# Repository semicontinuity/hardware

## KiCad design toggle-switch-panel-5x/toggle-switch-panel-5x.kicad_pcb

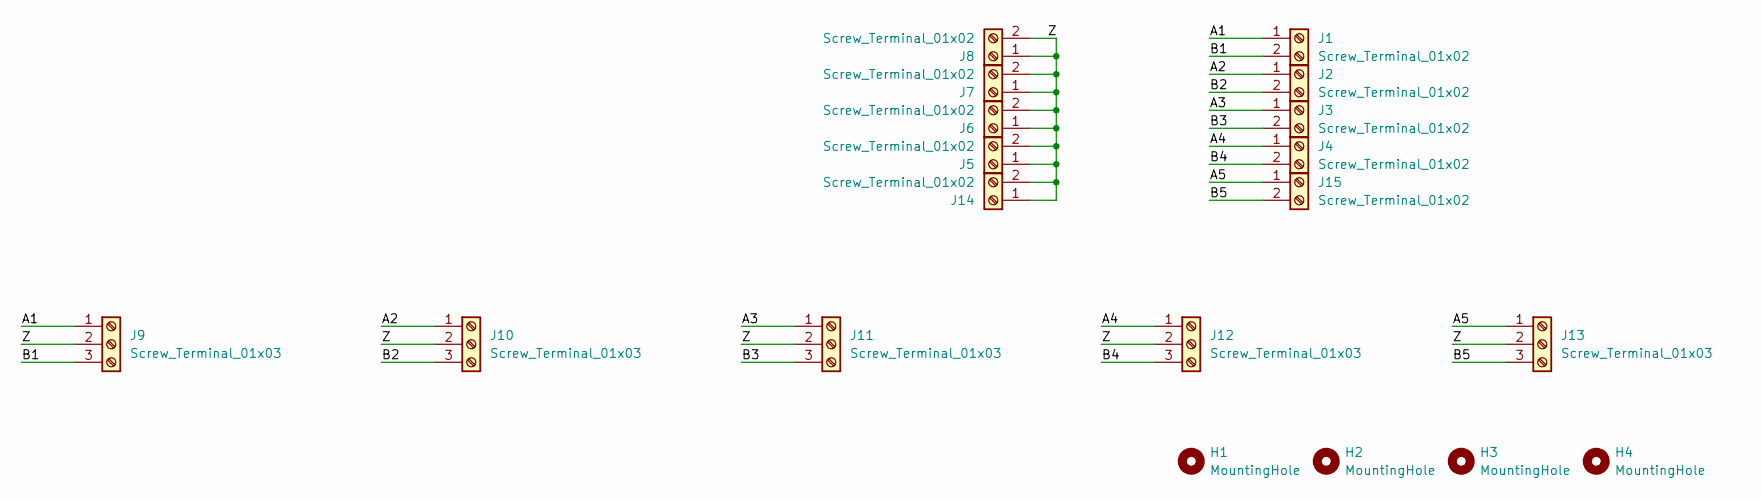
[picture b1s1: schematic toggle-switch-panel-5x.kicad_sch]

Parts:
H1, H2, H3, H4: MountingHole; MountingHole_3.2mm_M3
J1, J2, J3, J4, J5, J6, J7, J8, J14, J15: Screw_Terminal_01x02; TerminalBlock_Phoenix_MKDS-1,5-2_1x02_P5.00mm_Horizontal
J9, J10, J11, J12, J13: Screw_Terminal_01x03; TerminalBlock_Phoenix_MKDS-1,5-3_1x03_P5.00mm_Horizontal

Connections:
/A1: J1.1, J9.1
/A2: J2.1, J10.1
/A3: J3.1, J11.1
/A4: J4.1, J12.1
/A5: J13.1, J15.1
/B1: J1.2, J9.3
/B2: J2.2, J10.3
/B3: J3.2, J11.3
/B4: J4.2, J12.3
/B5: J13.3, J15.2
/Z: J5.1, J5.2, J6.1, J6.2, J7.1, J7.2, J8.1, J8.2, J9.2, J10.2, J11.2, J12.2, J13.2, J14.1, J14.2

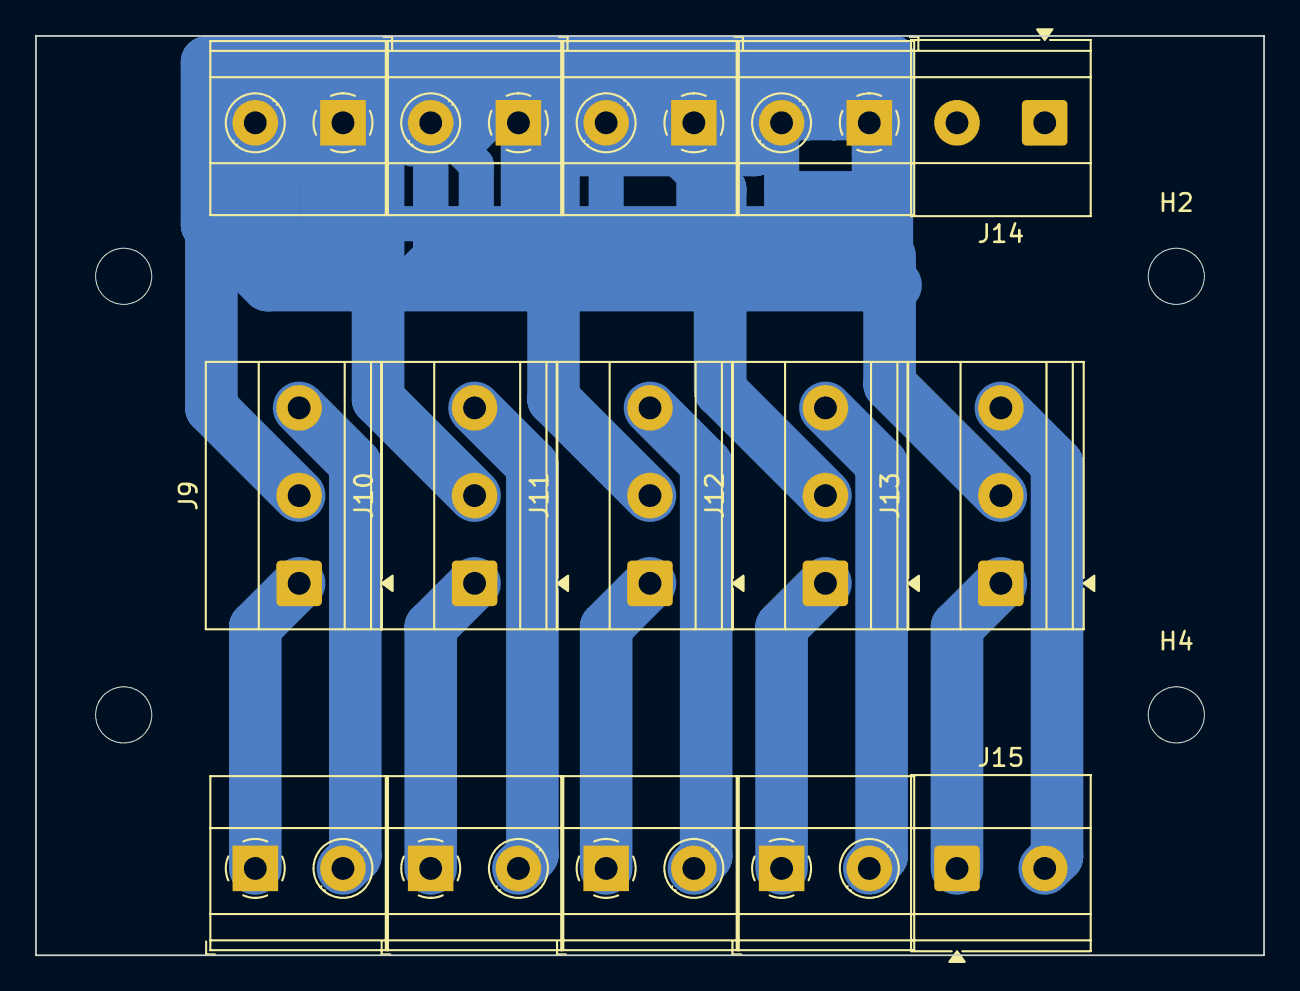
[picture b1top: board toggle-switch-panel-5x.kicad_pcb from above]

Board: 2 copper layers, 70.0 x 52.4 mm, 19 parts (0 on the bottom side), 11 nets.

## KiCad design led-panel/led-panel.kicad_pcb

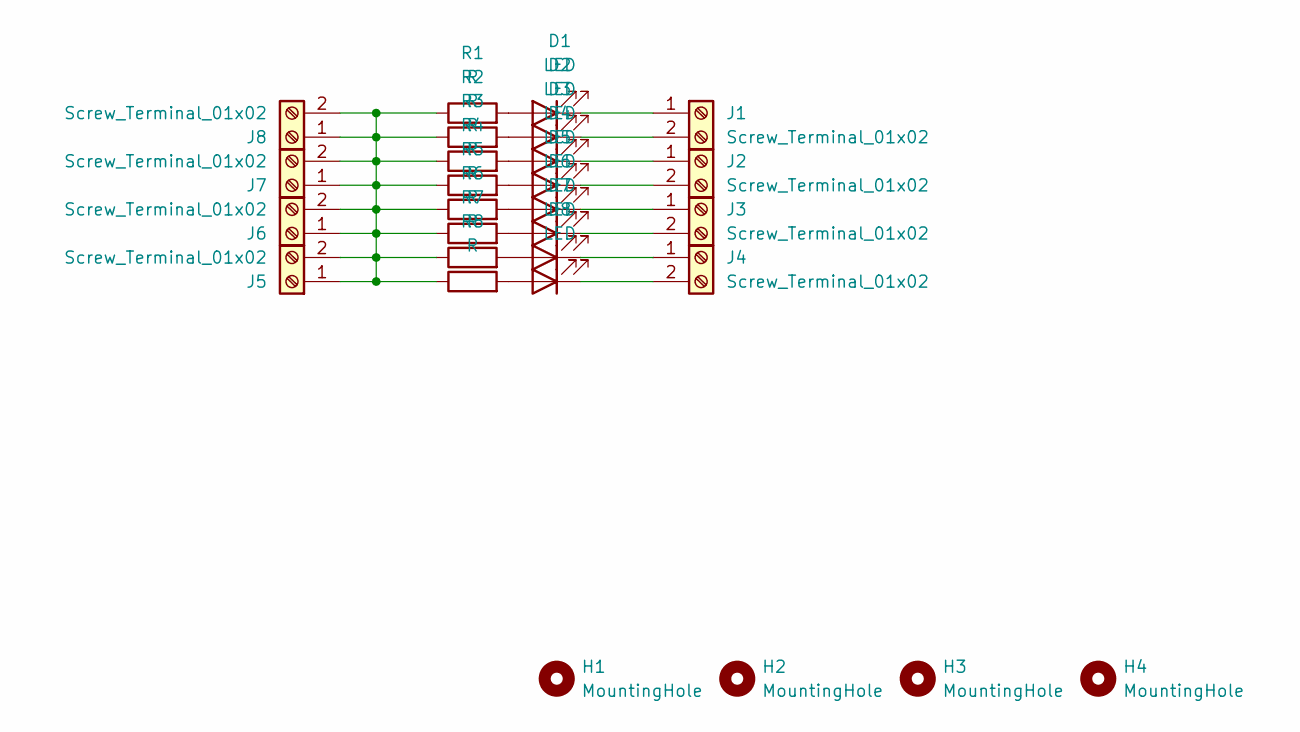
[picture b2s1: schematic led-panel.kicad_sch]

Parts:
D1, D2, D3, D4, D5, D6, D7, D8: LED; LED_D3.0mm
H1, H2, H3, H4: MountingHole; MountingHole_3.2mm_M3
J1, J2, J3, J4, J5, J6, J7, J8: Screw_Terminal_01x02; TerminalBlock_Phoenix_MKDS-1,5-2_1x02_P5.00mm_Horizontal
R1, R2, R3, R4, R5, R6, R7, R8: R; R_Axial_DIN0411_L9.9mm_D3.6mm_P20.32mm_Horizontal

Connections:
unnamed: D1.2 (A), R1.2
unnamed: D1.1 (K), J1.1
unnamed: D2.2 (A), R2.2
unnamed: D2.1 (K), J1.2
unnamed: D3.2 (A), R3.2
unnamed: D3.1 (K), J2.1
unnamed: D4.2 (A), R4.2
unnamed: D4.1 (K), J2.2
unnamed: D5.2 (A), R5.2
unnamed: D5.1 (K), J3.1
unnamed: D6.2 (A), R6.2
unnamed: D6.1 (K), J3.2
unnamed: D7.2 (A), R7.2
unnamed: D7.1 (K), J4.1
unnamed: D8.2 (A), R8.2
unnamed: D8.1 (K), J4.2
unnamed: J5.1, J5.2, J6.1, J6.2, J7.1, J7.2, J8.1, J8.2, R1.1, R2.1, R3.1, R4.1, R5.1, R6.1, R7.1, R8.1

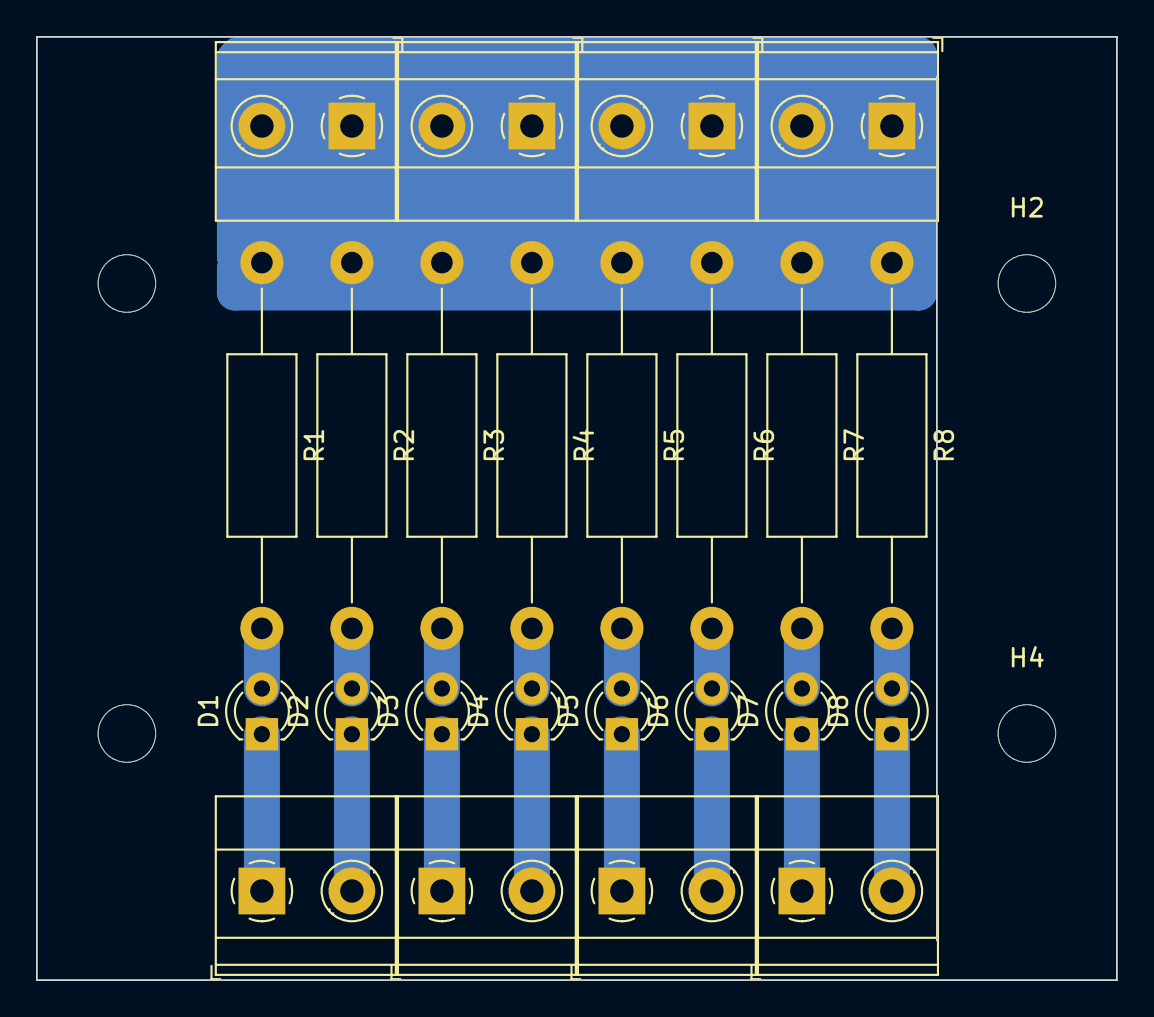
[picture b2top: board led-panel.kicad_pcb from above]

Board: 2 copper layers, 60.0 x 52.4 mm, 28 parts (0 on the bottom side), 17 nets.

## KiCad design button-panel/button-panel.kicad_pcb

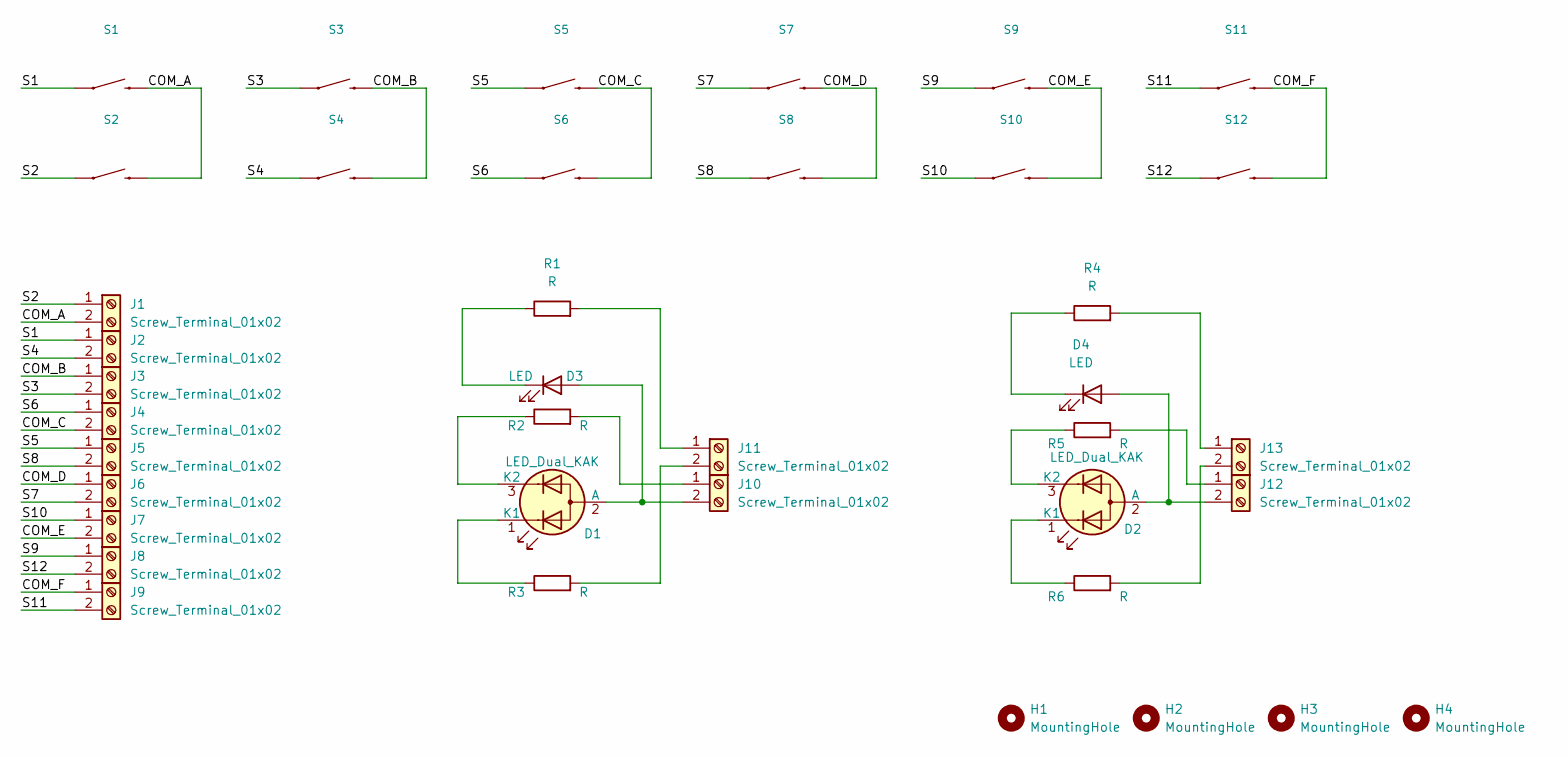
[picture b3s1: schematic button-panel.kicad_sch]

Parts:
D1, D2: LED_Dual_KAK; LED_D3.0mm-3
D3, D4: LED; LED_D3.0mm
H1, H2, H3, H4: MountingHole; MountingHole_3.2mm_M3
J1, J2, J3, J4, J5, J6, J7, J8, J9: Screw_Terminal_01x02; TerminalBlock_Phoenix_MKDS-1,5-2_1x02_P5.00mm_Horizontal
J10, J11, J12, J13: Screw_Terminal_01x02; TerminalBlock_Phoenix_PT-1,5-2-3.5-H_1x02_P3.50mm_Horizontal
R1, R2, R3, R4, R5, R6: R; R_0805_2012Metric
S1, S2, S3, S4, S5, S6, S7, S8, S9, S10, S11, S12: MOMENTARY-SWITCH-SPST-PTH-12MM; SW_PUSH-12mm

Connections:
/COM_A: J1.2, S1.2, S2.2
/COM_B: J3.1, S3.2, S4.2
/COM_C: J4.2, S5.2, S6.2
/COM_D: J6.1, S7.2, S8.2
/COM_E: J7.2, S9.2, S10.2
/COM_F: J9.1, S11.2, S12.2
/S1: J2.1, S1.1
/S2: J1.1, S2.1
/S3: J3.2, S3.1
/S4: J2.2, S4.1
/S5: J5.1, S5.1
/S6: J4.1, S6.1
/S7: J6.2, S7.1
/S8: J5.2, S8.1
/S9: J8.1, S9.1
/S10: J7.1, S10.1
/S11: J9.2, S11.1
/S12: J8.2, S12.1
unnamed: D1.1 (K1), R3.1
unnamed: D1.2 (A), D3.2 (A), J10.2
unnamed: D1.3 (K2), R2.1
unnamed: D2.1 (K1), R6.1
unnamed: D2.3 (K2), R5.1
unnamed: D3.1 (K), R1.1
unnamed: D4.1 (K), R4.1
unnamed: J10.1, R2.2
unnamed: J11.1, R1.2
unnamed: J11.2, R3.2
unnamed: J12.1, R5.2
unnamed: D2.2 (A), D4.2 (A), J12.2
unnamed: J13.1, R4.2
unnamed: J13.2, R6.2

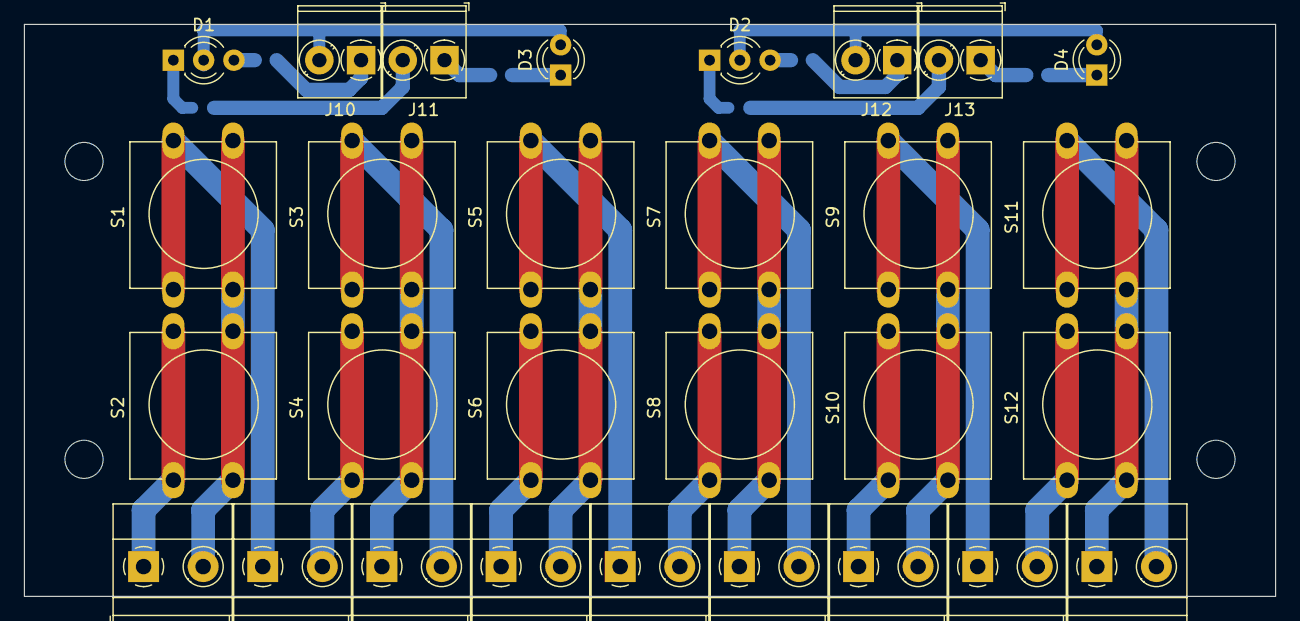
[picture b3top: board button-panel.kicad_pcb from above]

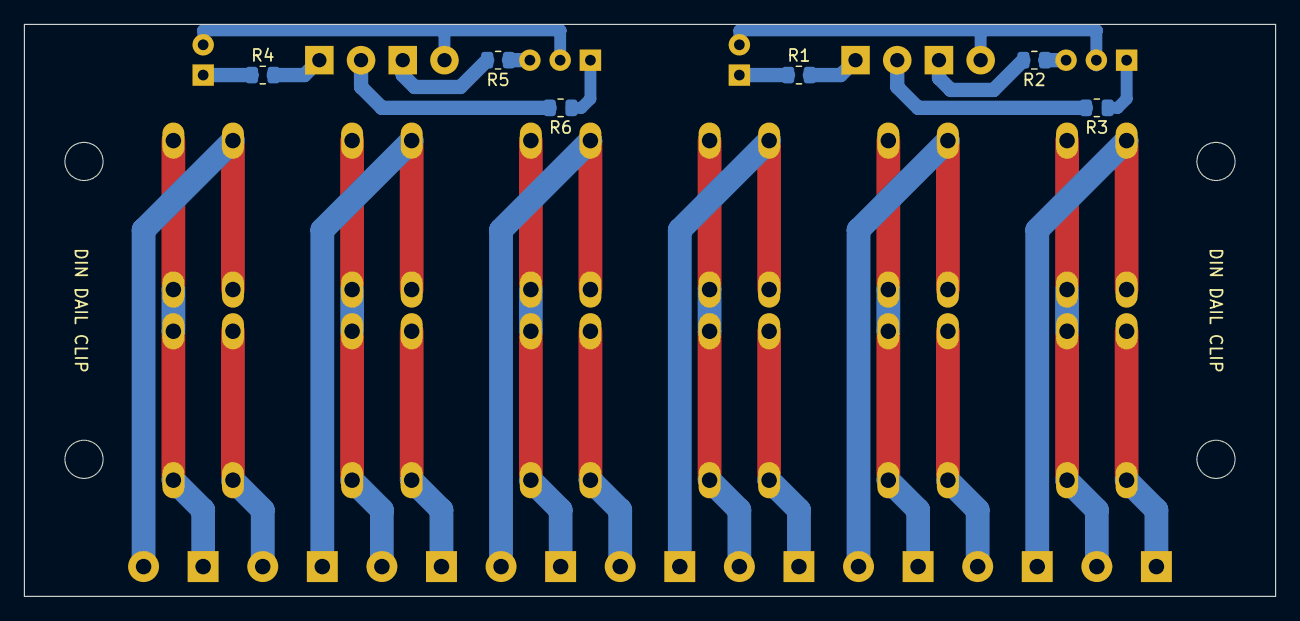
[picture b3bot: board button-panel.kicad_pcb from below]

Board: 2 copper layers, 105.0 x 48.0 mm, 39 parts (6 on the bottom side), 32 nets.

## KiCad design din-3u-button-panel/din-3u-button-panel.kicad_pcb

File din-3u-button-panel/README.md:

#### UI and connections

* 3U DIN rail enclosure (51mm)

Base board
```
   LED_A  LED_B  LED_C  VCC  VCC  LED_D  LED_E  LED_F
+--------------------------------------------------------+
|                                                        |
|                                                        |
|                                                        |
|                                                        |
|                                                        |
|                                                        |
|                                                        |
+--------------------------------------------------------+
   BTN_A  BTN_B  BTN_C  GND  GND  BTN_D  BTN_E  BTN_F

```

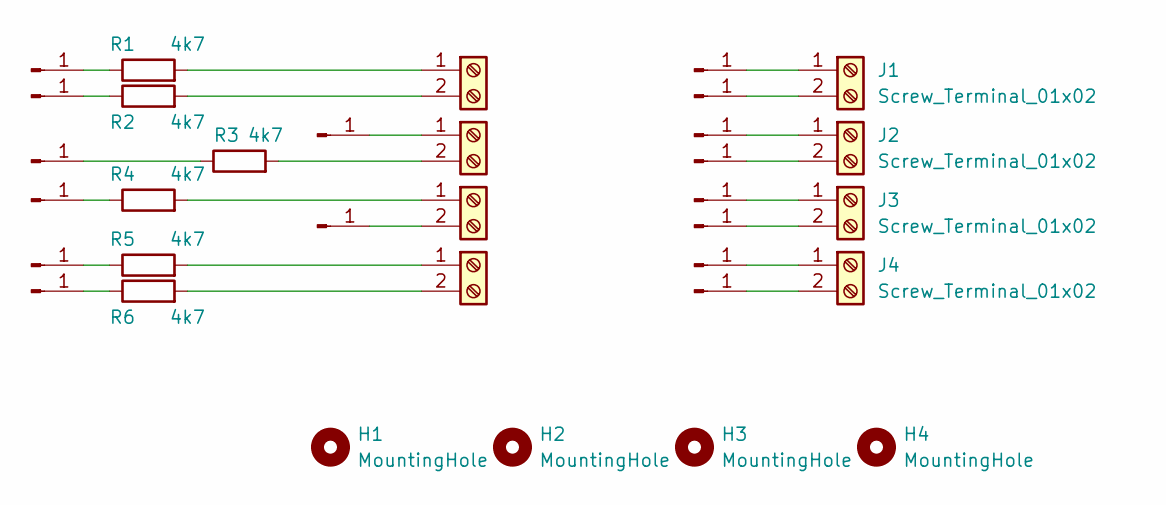
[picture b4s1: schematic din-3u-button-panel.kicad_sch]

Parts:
H1, H2, H3, H4: MountingHole; MountingHole_3.5mm
J1, J2, J3, J4: Screw_Terminal_01x02; TerminalBlock_Phoenix_MKDS-1,5-2-5.08_1x02_P5.08mm_Horizont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
J5, J10, J11, J12, J13, J14, J15, J16, J17, J18, J19, J20, J21, J22, J23, J24: Conn_01x01_Pin; Pin_D1.0mm_L10.0mm
J6: Z1; TerminalBlock_Phoenix_MKDS-1,5-2-5.08_1x02_P5.08mm_Horizont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
J7: Z2; TerminalBlock_Phoenix_MKDS-1,5-2-5.08_1x02_P5.08mm_Horizont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
J8: Z3; TerminalBlock_Phoenix_MKDS-1,5-2-5.08_1x02_P5.08mm_Horizont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
J9: Z4; TerminalBlock_Phoenix_MKDS-1,5-2-5.08_1x02_P5.08mm_Horizont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
R1, R2, R3, R4, R5, R6: 4k7; R_Axial_DIN0207_L6.3mm_D2.5mm_P15.24mm_Horizontal

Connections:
unnamed: J1.1, J17.1
unnamed: J1.2, J18.1
unnamed: J2.2, J20.1
unnamed: J5.1, R1.1
unnamed: J6.1, R1.2
unnamed: J6.2, R2.2
unnamed: J7.2, R3.2
unnamed: J8.1, R4.2
unnamed: J9.1, R5.2
unnamed: J9.2, R6.2
unnamed: J10.1, R2.1
unnamed: J7.1, J11.1
unnamed: J12.1, R3.1
unnamed: J13.1, R4.1
unnamed: J8.2, J14.1
unnamed: J15.1, R5.1
unnamed: J16.1, R6.1
unnamed: J2.1, J19.1
unnamed: J3.1, J21.1
unnamed: J3.2, J22.1
unnamed: J4.1, J23.1
unnamed: J4.2, J24.1

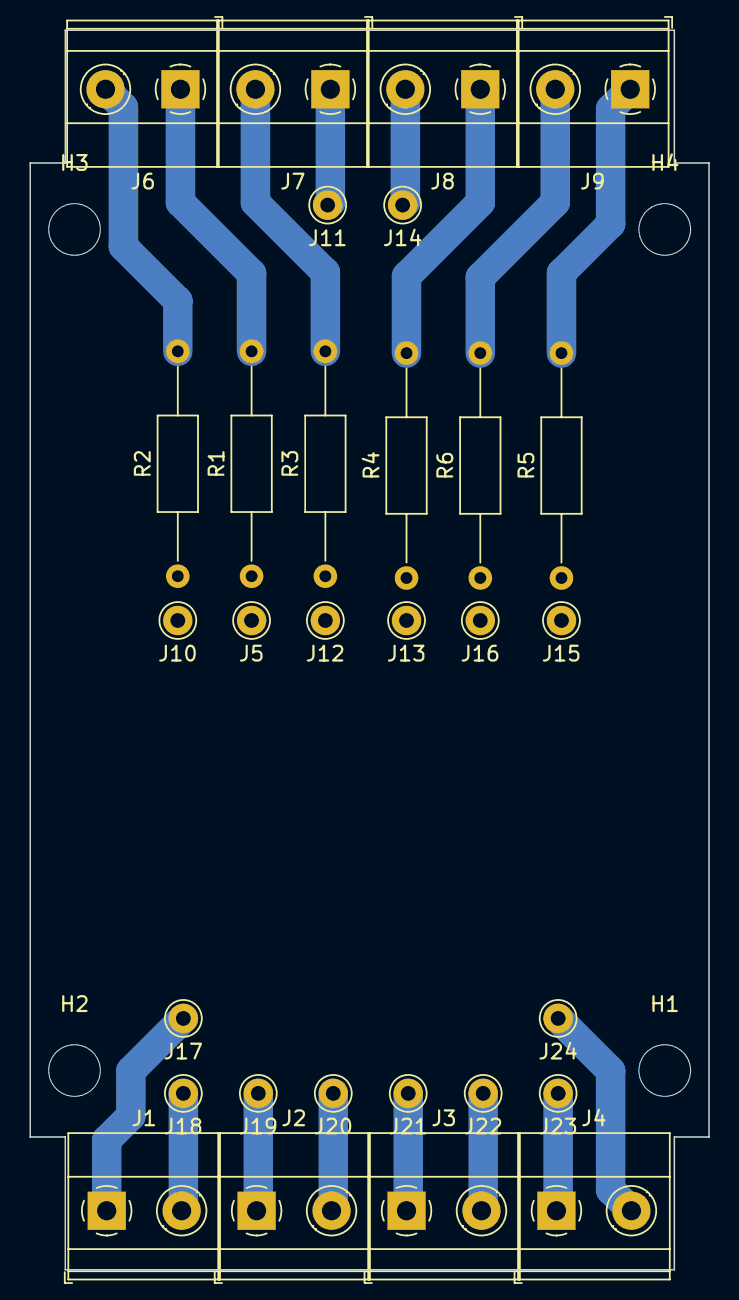
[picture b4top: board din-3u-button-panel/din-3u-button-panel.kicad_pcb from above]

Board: 2 copper layers, 46.0 x 84.0 mm, 34 parts (0 on the bottom side), 22 nets.

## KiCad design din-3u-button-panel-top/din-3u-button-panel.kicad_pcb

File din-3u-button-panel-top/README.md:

#### UI and connections

* 3U DIN rail enclosure (51mm)

Front panel
```
+--------------------------------------------------------+
|                                                        |
|  (A) Yellow          (B) Yellow         (C) Red        | --
|                                                        | 16mm
|  (D) Green           (E) Green          (F) White      | --
|                                                        |
+--------------------------------------------------------+
    |       16mm       |
```

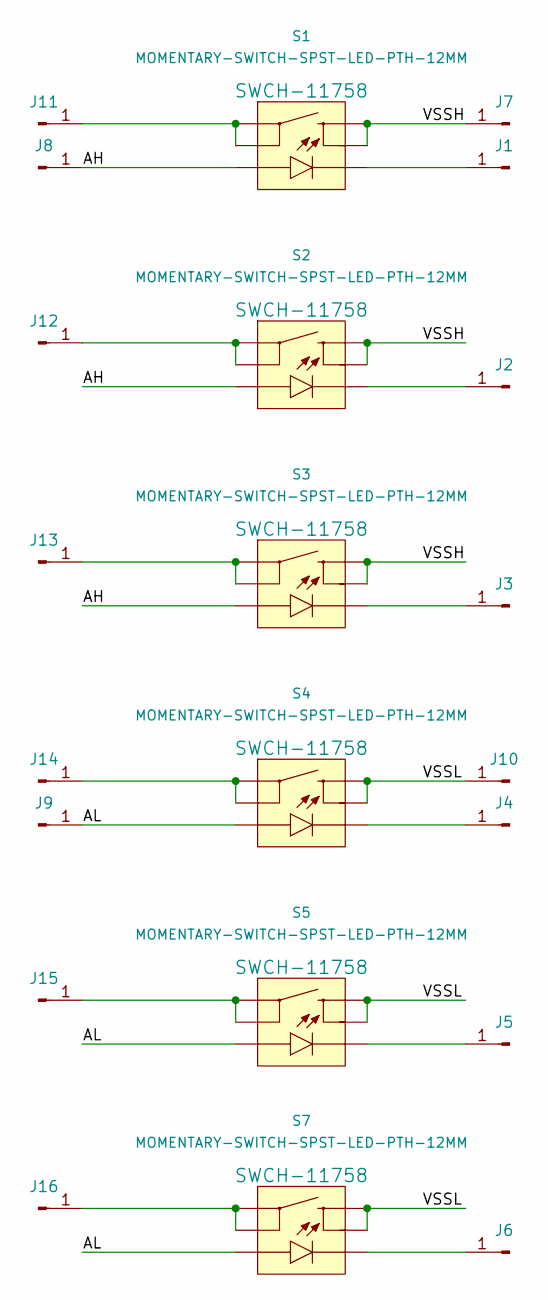
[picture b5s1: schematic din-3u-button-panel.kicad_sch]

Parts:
J1, J2, J3, J4, J5, J6, J7, J8, J9, J10, J11, J12, J13, J14, J15, J16: Conn_01x01_Pin; PinHeader_1x01_P2.54mm_Vertical
S1, S2, S3, S4, S5, S7: MOMENTARY-SWITCH-SPST-LED-PTH-12MM; TACTILE_SWITCH_LED_PTH_12MM

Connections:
/AH: J8.1, S1.A, S2.A, S3.A
/AL: J9.1, S4.A, S5.A, S7.A
/VSSH: J7.1, S1.1, S1.2, S2.1, S2.2, S3.1, S3.2
/VSSL: J10.1, S4.1, S4.2, S5.1, S5.2, S7.1, S7.2
unnamed: J1.1, S1.C
unnamed: J2.1, S2.C
unnamed: J3.1, S3.C
unnamed: J4.1, S4.C
unnamed: J5.1, S5.C
unnamed: J6.1, S7.C
unnamed: J11.1, S1.3, S1.4 (1)
unnamed: J12.1, S2.3, S2.4 (1)
unnamed: J13.1, S3.3, S3.4 (1)
unnamed: J14.1, S4.3, S4.4 (1)
unnamed: J15.1, S5.3, S5.4 (1)
unnamed: J16.1, S7.3, S7.4 (1)

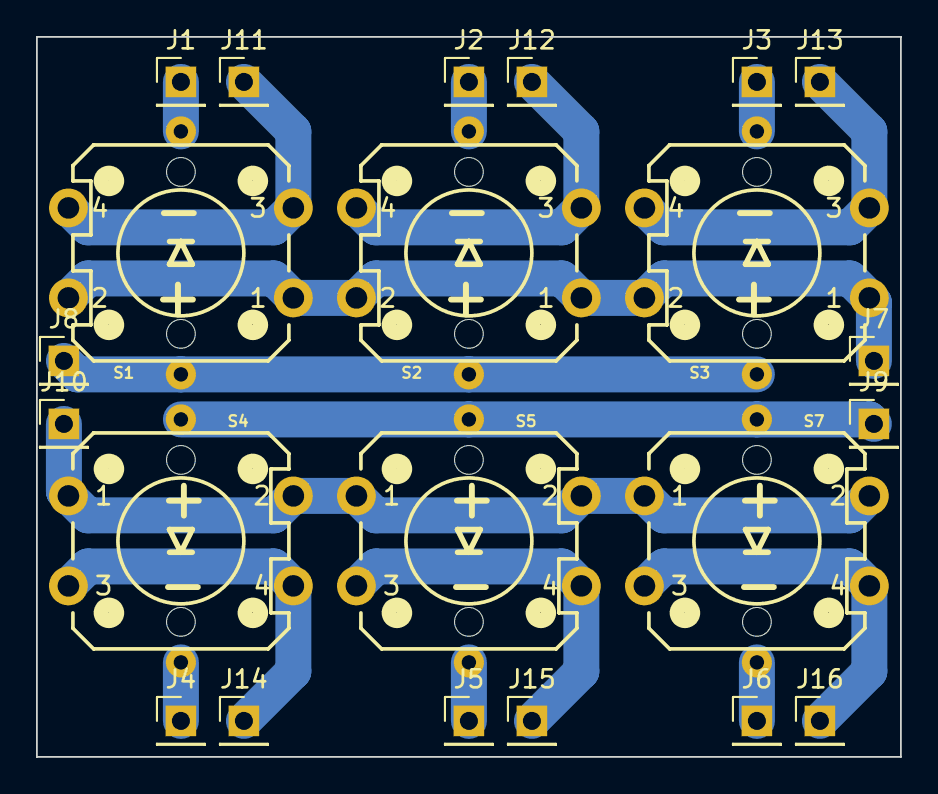
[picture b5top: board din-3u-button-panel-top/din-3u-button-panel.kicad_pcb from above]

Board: 2 copper layers, 48.0 x 40.0 mm, 22 parts (0 on the bottom side), 16 nets.

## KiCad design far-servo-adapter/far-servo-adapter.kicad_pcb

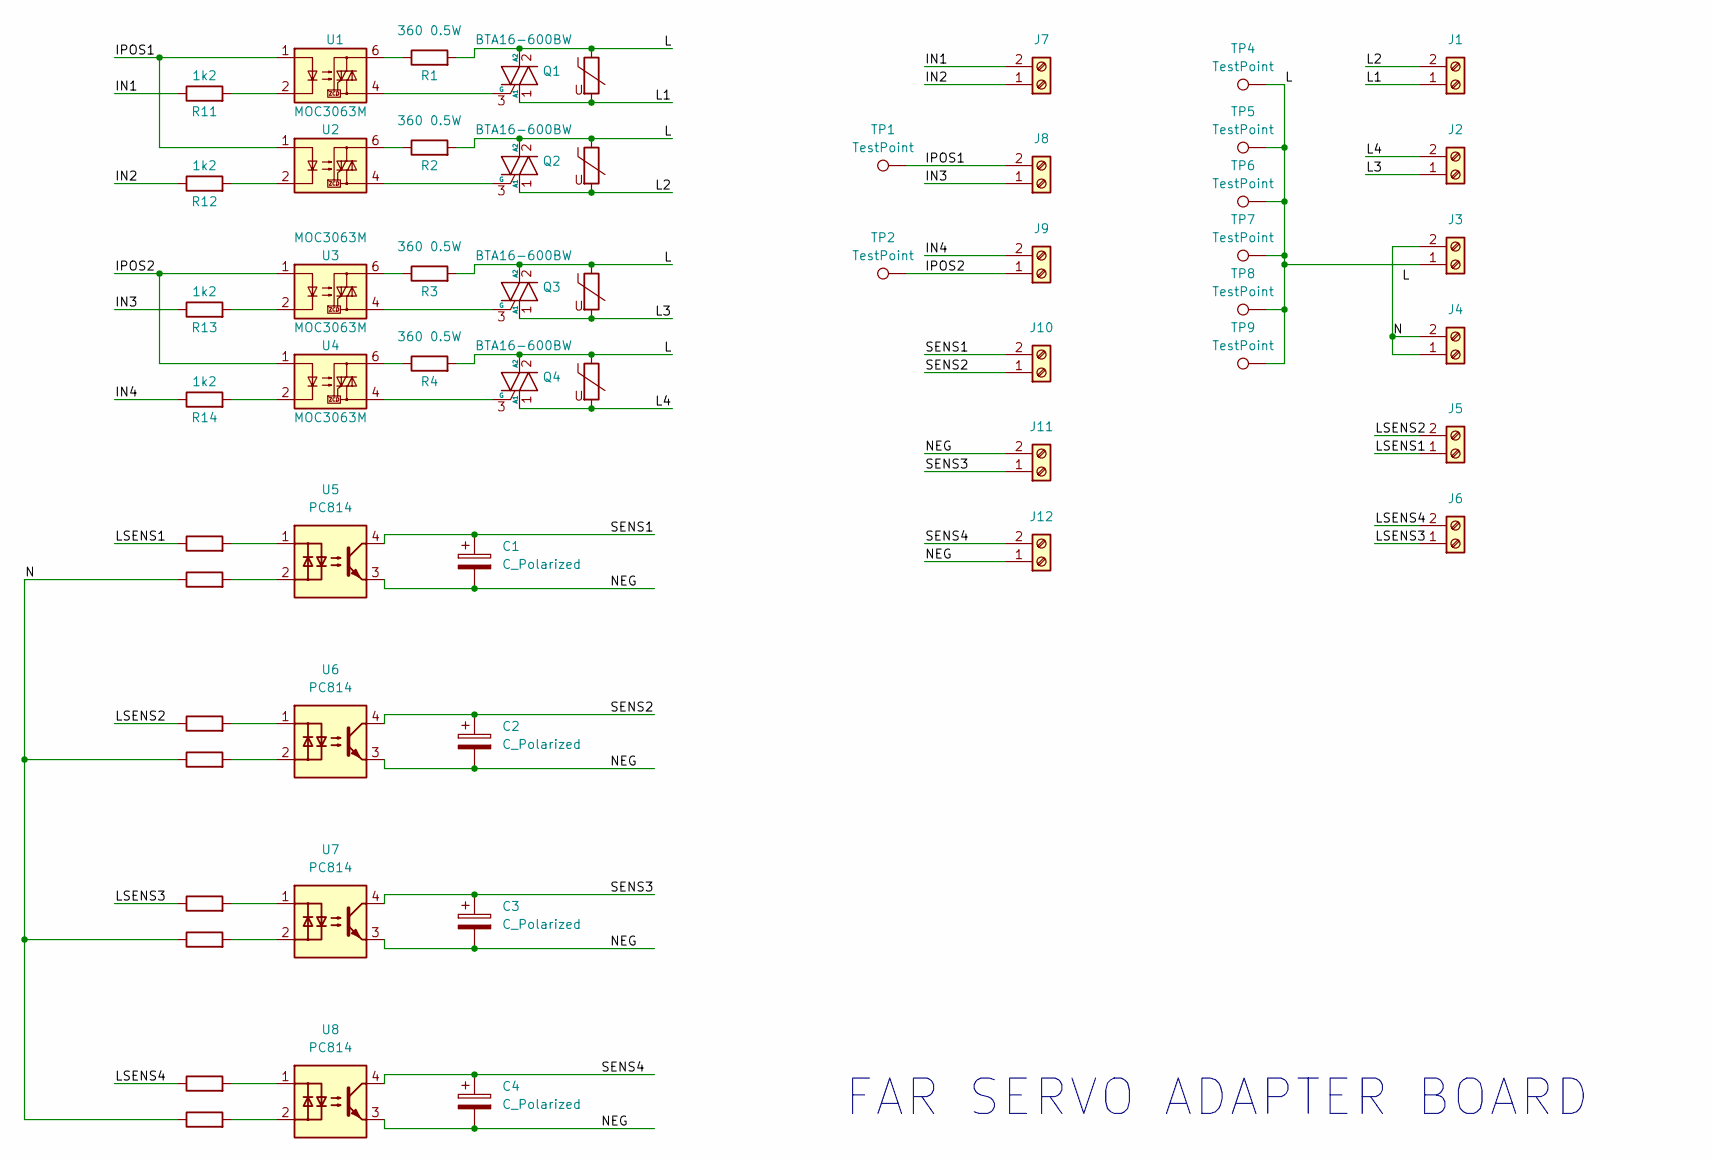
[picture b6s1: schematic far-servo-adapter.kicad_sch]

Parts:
C1, C2, C3, C4: C_Polarized; CP_Radial_D5.0mm_P2.50mm
J1, J2, J3, J4, J5, J6, J7, J8, J9, J10, J11, J12: Screw_Terminal_01x02; TerminalBlock_Phoenix_MKDS-1,5-2_1x02_P5.00mm_Horizontal
Q1, Q2, Q3, Q4: BTA16-600BW; TO-220-3_Vertical_Staggered
R1, R2, R3, R4: 360 0.5W; R_Axial_DIN0309_L9.0mm_D3.2mm_P20.32mm_Horizontal
R5, R6, R7, R8, R9, R10, R15, R16: 100k; R_Axial_DIN0516_L15.5mm_D5.0mm_P20.32mm_Horizontal
R11, R12, R13, R14: 1k2; R_Axial_DIN0207_L6.3mm_D2.5mm_P10.16mm_Horizontal
RV1, RV2, RV3, RV4: 275V; RV_Disc_D9mm_W4.2mm_P5mm
TP1, TP2, TP4, TP5, TP6, TP7, TP8, TP9: TestPoint; Pin_D1.0mm_L10.0mm
U1, U2, U3, U4: MOC3063M; DIP-6_W7.62mm
U5, U6, U7, U8: PC814; DIP-4_W7.62mm

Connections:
/IN1: J7.2, R11.1
/IN2: J7.1, R12.1
/IN3: J8.1, R13.1
/IN4: J9.2, R14.1
/IPOS1: J8.2, TP1.1, U1.1, U2.1
/IPOS2: J9.1, TP2.1, U3.1, U4.1
/L: J3.1, Q1.2 (A2), Q2.2 (A2), Q3.2 (A2), Q4.2 (A2), R1.2, R2.2, R3.2, R4.2, RV1.1, RV2.1, RV3.1, RV4.1, TP4.1, TP5.1, TP6.1, TP7.1, TP8.1, TP9.1
/L1: J1.1, Q1.1 (A1), RV1.2
/L2: J1.2, Q2.1 (A1), RV2.2
/L3: J2.1, Q3.1 (A1), RV3.2
/L4: J2.2, Q4.1 (A1), RV4.2
/LSENS1: J5.1, R5.1
/LSENS2: J5.2, R7.1
/LSENS3: J6.1, R9.1
/LSENS4: J6.2, R15.1
/N: J3.2, J4.1, J4.2, R6.1, R8.1, R10.1, R16.1
/NEG: C1.2, C2.2, C3.2, C4.2, J11.2, J12.1, U5.3, U6.3, U7.3, U8.3
/SENS1: C1.1, J10.2, U5.4
/SENS2: C2.1, J10.1, U6.4
/SENS3: C3.1, J11.1, U7.4
/SENS4: C4.1, J12.2, U8.4
unnamed: Q1.3 (G), U1.4
unnamed: Q2.3 (G), U2.4
unnamed: Q3.3 (G), U3.4
unnamed: Q4.3 (G), U4.4
unnamed: R1.1, U1.6
unnamed: R2.1, U2.6
unnamed: R3.1, U3.6
unnamed: R4.1, U4.6
unnamed: R5.2, U5.1
unnamed: R6.2, U5.2
unnamed: R7.2, U6.1
unnamed: R8.2, U6.2
unnamed: R9.2, U7.1
unnamed: R10.2, U7.2
unnamed: R11.2, U1.2
unnamed: R12.2, U2.2
unnamed: R13.2, U3.2
unnamed: R14.2, U4.2
unnamed: R15.2, U8.1
unnamed: R16.2, U8.2

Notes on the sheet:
FAR SERVO ADAPTER BOARD

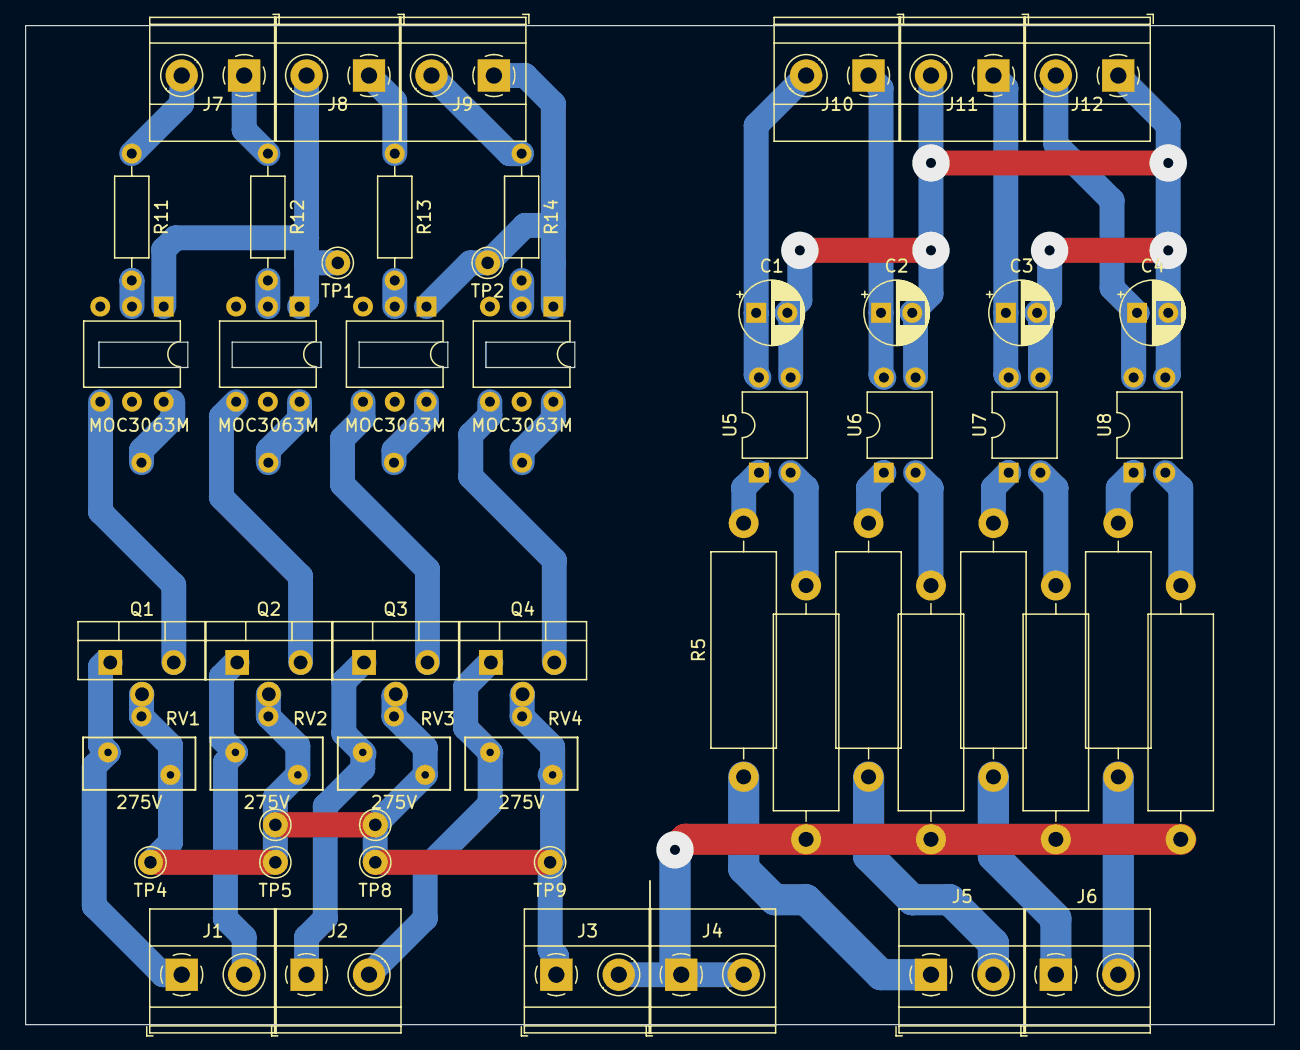
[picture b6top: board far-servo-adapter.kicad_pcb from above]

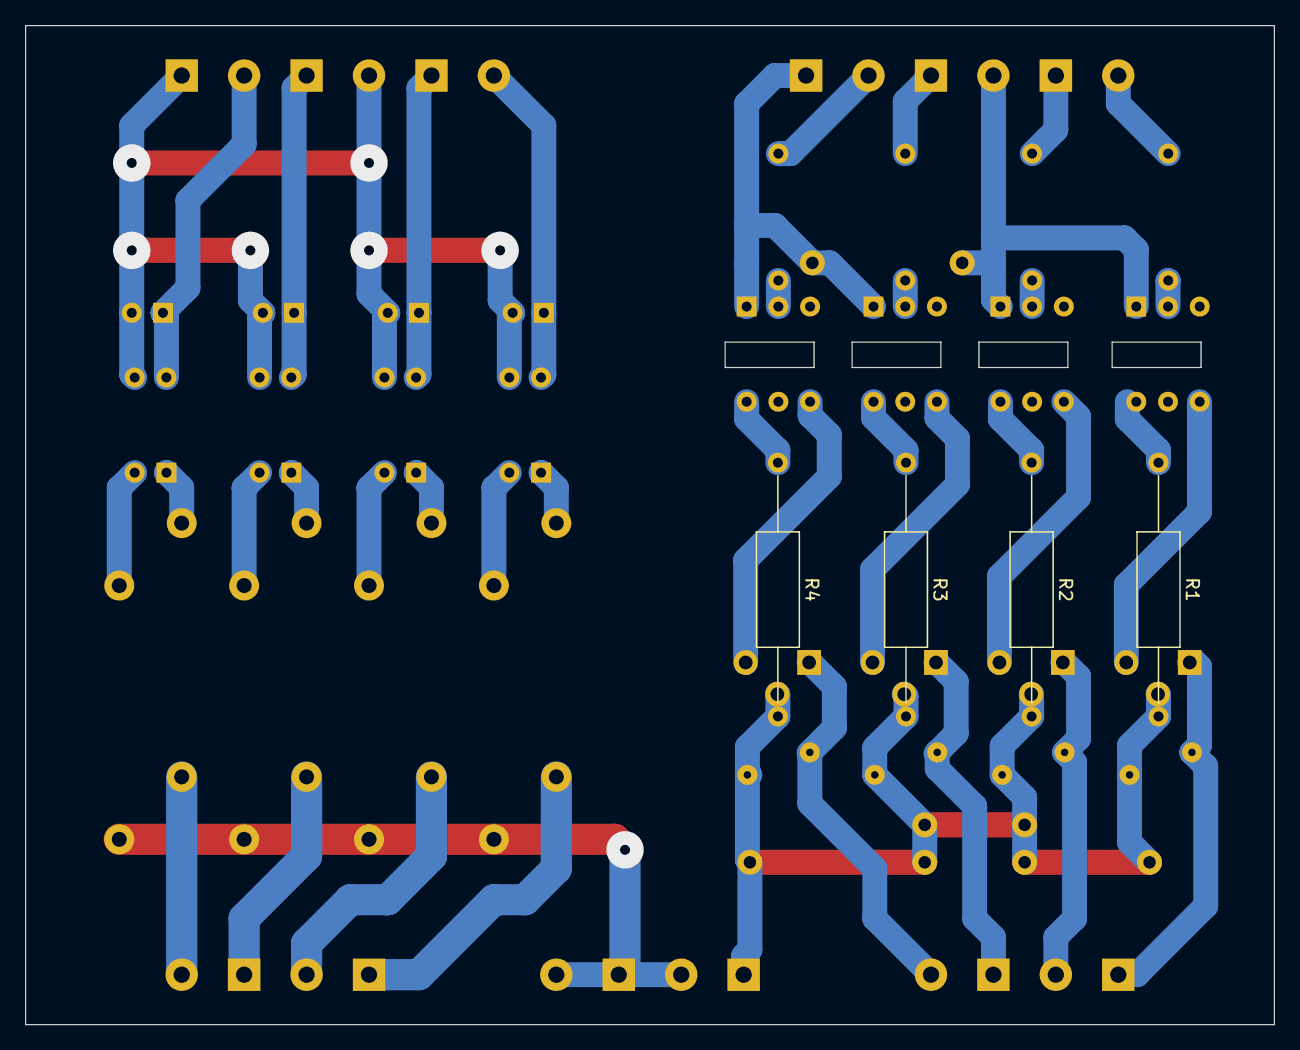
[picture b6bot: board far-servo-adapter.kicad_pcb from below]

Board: 2 copper layers, 100.0 x 80.0 mm, 56 parts (4 on the bottom side), 41 nets.

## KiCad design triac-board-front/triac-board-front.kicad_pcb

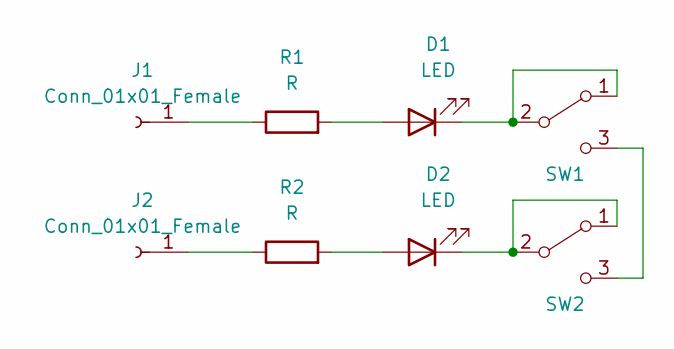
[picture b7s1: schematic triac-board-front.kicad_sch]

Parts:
D1, D2: LED; LED_D3.0mm
J1, J2: Conn_01x01_Female; SolderWire-0.5sqmm_1x01_D0.9mm_OD2.1mm
R1, R2: R; R_Axial_DIN0207_L6.3mm_D2.5mm_P7.62mm_Horizontal
SW1, SW2: SW_SPDT; PinHeader_1x03_P2.54mm_Vertical

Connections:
unnamed: D1.1 (K), SW1.1 (A), SW1.2 (B)
unnamed: D1.2 (A), R1.2
unnamed: D2.1 (K), SW2.1 (A), SW2.2 (B)
unnamed: D2.2 (A), R2.2
unnamed: J1.1, R1.1
unnamed: J2.1, R2.1
unnamed: SW1.3 (C), SW2.3 (C)

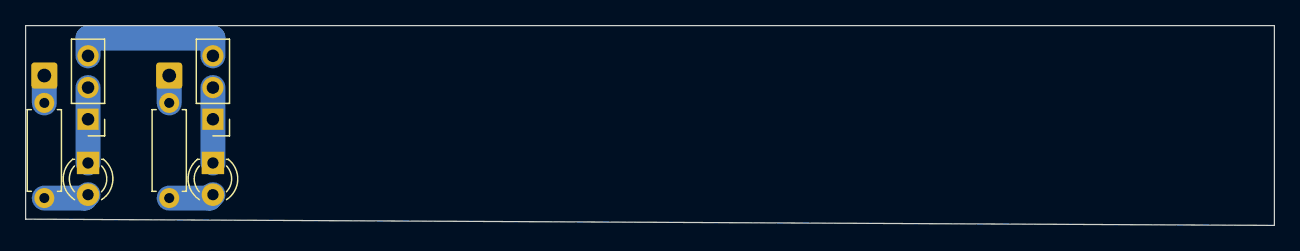
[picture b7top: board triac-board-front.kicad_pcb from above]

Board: 2 copper layers, 100.0 x 16.0 mm, 8 parts (0 on the bottom side), 7 nets.
